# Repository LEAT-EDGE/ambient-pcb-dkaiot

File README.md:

# Ambient DKAIoT Mainboard PCB

Mainboard PCB for the [Ambient project](https://github.com/LEAT-EDGE/ambient).

<div style="display: flex; justify-content: center; gap: 20px;">

</div>

## Main features

- Microcontroller from the STM32L4 or STM32U5 families (LQFP-64 package, no SMPS)
  - STM32L496RG: low-power, Cortex-M4F 80 MHz, 320 KiB SRAM, 1 MiB Flash
  - STM32U595RI: ultra-low-power, Cortex-M33 160 MHz, 2.5 MiB SRAM, 2 MiB Flash
- LoRa modem (Ebyte E22-900M22S)
- GNSS module (Quectel L96-M33)
- Temperature, humidity and pressure (Bosch BME280)
- Micro-SD card reader

The design also provides empty footprints for several other sensors which are not populated in the Ambient variant:
- Light sensor (LITEON LTR-303ALS-01)
- MEMS microphone (Knowles SPH0645LM4H)
- Indoor air quality (Sensirion SGP30)
- Hall effect (Texas Instruments DRV5023AJQLPG)
- Barometer and altimeter (HopeRF HP203B)
- 3-axis accelerometer, 3-axis gyroscope, 3-axis magnetometer (TDK ICM-20948)
- 3-axis accelerometer, 3-axis magnetometer (STMicroelectronics LSM303AH)
- 3-axis accelerometer (Kionix KX023-1025-FR)
- 3-axis accelerometer (Kionix KXTJ3-1057)

## Project structure
- `/` (repository root): KiCad project
- `gerbers/`: Gerbers generated from the KiCad project
- `libraries/`: KiCad libraries of symbols, footprints and 3D models for components not found in the KiCad official repository
- `pdf/`: Schematics generated from the KiCad project
- `png/`: Screenshots of the KiCad 3D render
- `webp/`: Pictures of the actual board

## Firmware

### Firmware sources

Refer to <https://github.com/LEAT-EDGE/ambient-firmware-zephyr> for the new, Zephyr RTOS-based firmware (compatible with both STM32L4 and STM32U5),
and to <https://github.com/LEAT-EDGE/ambient-firmware-arduino> for the old Arduino-based firmware (not compatible with STM32U5).

### Updating the firmware

In order to flash the firmware, put the microcontroller in bootloader DFU mode by holding the BOOT button (right next to the USB port) and pressing the RESET button (next to the BOOT button), then releasing the BOOT button after a couple of seconds. Alternatively, you can hold the BOOT button while plugging the USB cable in, and releasing it after a couple of seconds.

[dfu-util](https://dfu-util.sourceforge.net/) can then be used to update the firmware.
It is called automatically by the `west flash` command when using the Zephyr-based firmware, or by the Arduino IDE's Upload button when using the Arduino-based firmware.

On Windows, for `dfu-util` to work properly, it is recommended to use the WinUSB driver. [Zadig](https://zadig.akeo.ie/) can be used to change the driver of the `STM32 BOOTLOADER` device to WinUSB.

On Linux, for a standard user to have access to the USB device, you may have to install a [udev rules file](https://github.com/LEAT-EDGE/ambient-firmware-arduino/blob/master/stm32dfu.udev.rules) in `/etc/udev/rules.d/`.

An SWD probe (e.g., STLINK V2 or V3) can also be used through the J7 debug header. Programming and debugging can then be performed using [OpenOCD](https://openocd.org/)

## Connectors and headers

### J1: UART

Exposes the `PA2` and `PA3` pins for the `USART2` peripheral of the microcontroller for debugging purposes.

Pinout:

| Pin   | Net           |
|-------|---------------|
| **4** | `V_PERIPH_3V` |
| **3** | `PA2_TX`      |
| **2** | `PA3_RX`      |
| **1** | `GND`         |

### J2J14

Main connector for the [audio capture and energy management daughterboard](https://github.com/LEAT-EDGE/ambient-pcb-audiopower).

Exposes the I2S bus (`SAI1B`), an I2C bus (`I2C2`), the 1.8V (`VDD_1V8`) and 3.0V (`V_PERIPH_3V`) peripheral supplies, 2 GPIOs (`PA10`, `PA15`) and the microcontroller reset signal (`MCU_RESET`, for reed switch reset trigger).

Pinout:

| Pin    | Net           | Pin    | Net            |
|--------|---------------|--------|----------------|
| **11** | `GND`         | **12** | `MCU_RESET`    |
| **9**  | `SAI_FS`      | **10** | `EXT_MIC_IO_2` |
| **7**  | `SAI_SD`      | **8**  | `EXT_MIC_IO_2` |
| **5**  | `SAI_MCLK`    | **6**  | `I2C2_SCL`     |
| **3**  | `SAI_SCK`     | **4**  | `I2C2_SDA`     |
| **1**  | `V_PERIPH_3V` | **2**  | `VDD_1V8`      |

### J3: ADC/DAC

Unused in the Ambient variant.

Exposes 2 GPIOs (`PA5`, `PC2`) that provides access to the microcontroller's ADC and DAC channels.

Pinout:

| Pin   | Net           |
|-------|---------------|
| **2** | `PC2_ADC`     |
| **1** | `PA5_DAC_ADC` |

### J4: BATTERY

Power input to the board and output of the USB charging circuit.

The [audio capture and energy management daughterboard](https://github.com/LEAT-EDGE/ambient-pcb-audiopower) connects to this header with its J3 connector.

| Pin   | Net     |
|-------|---------|
| **2** | `+BATT` |
| **1** | `GND`   |

### J5: SOLAR

Unused in the Ambient variant.

Power input to the charging circuit

Pinout:

| Pin   | Net     |
|-------|---------|
| **2** | `SOLAR` |
| **1** | `GND`   |

### J7: SWD

Exposes the SWD pins of the microcontroller for debugging purposes.

Pinout:

| Pin   | Net         |
|-------|-------------|
| **5** | `3V`        |
| **4** | `SWCLK`     |
| **3** | `MCU_RESET` |
| **2** | `SWDIO`     |
| **1** | `GND`       |

### J11: BATT1

Unused in the Ambient variant.

1st Li-ion cell connector, behind protection circuit.

| Pin   | Net         |
|-------|-------------|
| **2** | `+BATT1_IN` |
| **1** | `-BATT1_IN` |

### J12: BATT2

Unused in the Ambient variant.

2nd Li-ion cell connector, behind protection circuit.

| Pin   | Net         |
|-------|-------------|
| **2** | `+BATT2_IN` |
| **1** | `-BATT2_IN` |

### J20/J21/J22/J23: antenna header

Used to attach the [LoRa antenna mezzanine PCB](https://github.com/LEAT-EDGE/ambient-pcb-antenna).

| Pin     | Net       |
|---------|-----------|
| **J20** | `E22_ANT` |
| **J21** | `GND`     |
| **J22** | `GND`     |
| **J23** | `GND`     |

## Fabrication notes

### PCB

Standard 2-layer 0.8mm stackup:
- 2 layers (front/back),
- 0.8mm thickness,
- 1oz copper,
- FR-4 dielectric,
- HASL finish.

No special requirements, any solder mask and silkscreen color.

Gerbers are provided in the `gerbers/` directory but can be re-generated from the KiCad project.

### Assembly

Recommended automated assembly for top-side only.

Manual assembly for top side:
- J20, J21, J22 and J23 pins (through-hole), to be inserted or cut flush with the back side.

Manual assembly for bottom side:
- C16 and C42 capacitors (SMD),
- J2J14 and J4 connectors (through-hole).

## Testing

Currently, no testing process and firmware is provided. Proper operation of the board can be checked by running the Ambient application firmware.

Short checklist (non exhaustive):
- [ ] USB DFU bootloader detection
- [ ] USB DFU bootloader firmware programming
- [ ] Application firmware boot
- [ ] USB CDC-ACM logs
- [ ] LoRa modem initialization
- [ ] LoRaWAN join
- [ ] LoRaWAN send
- [ ] GNSS time synchronization
- [ ] BME280 temperature read
- [ ] SD card initialization and file write
- [ ] Daughterboard communication:
  - [ ] INA3221 initialization
  - [ ] INA3221 battery/solar current/voltage read
  - [ ] ADC3101 initialization
  - [ ] I2S initialization
  - [ ] I2S audio signal capture

## Acknowledgment

Original circuit design by [@nguyenmanhthao996tn](https://github.com/nguyenmanhthao996tn) in Altium.

The schematics and PCB have been re-designed from scratch in KiCad, while keeping the original circuit ideas, BOM, and component placement to be used as a drop-in replacement.

This project has received funding from [Université Côte d'Azur](https://leat.univ-cotedazur.fr/) and [CERN](https://home.cern/).

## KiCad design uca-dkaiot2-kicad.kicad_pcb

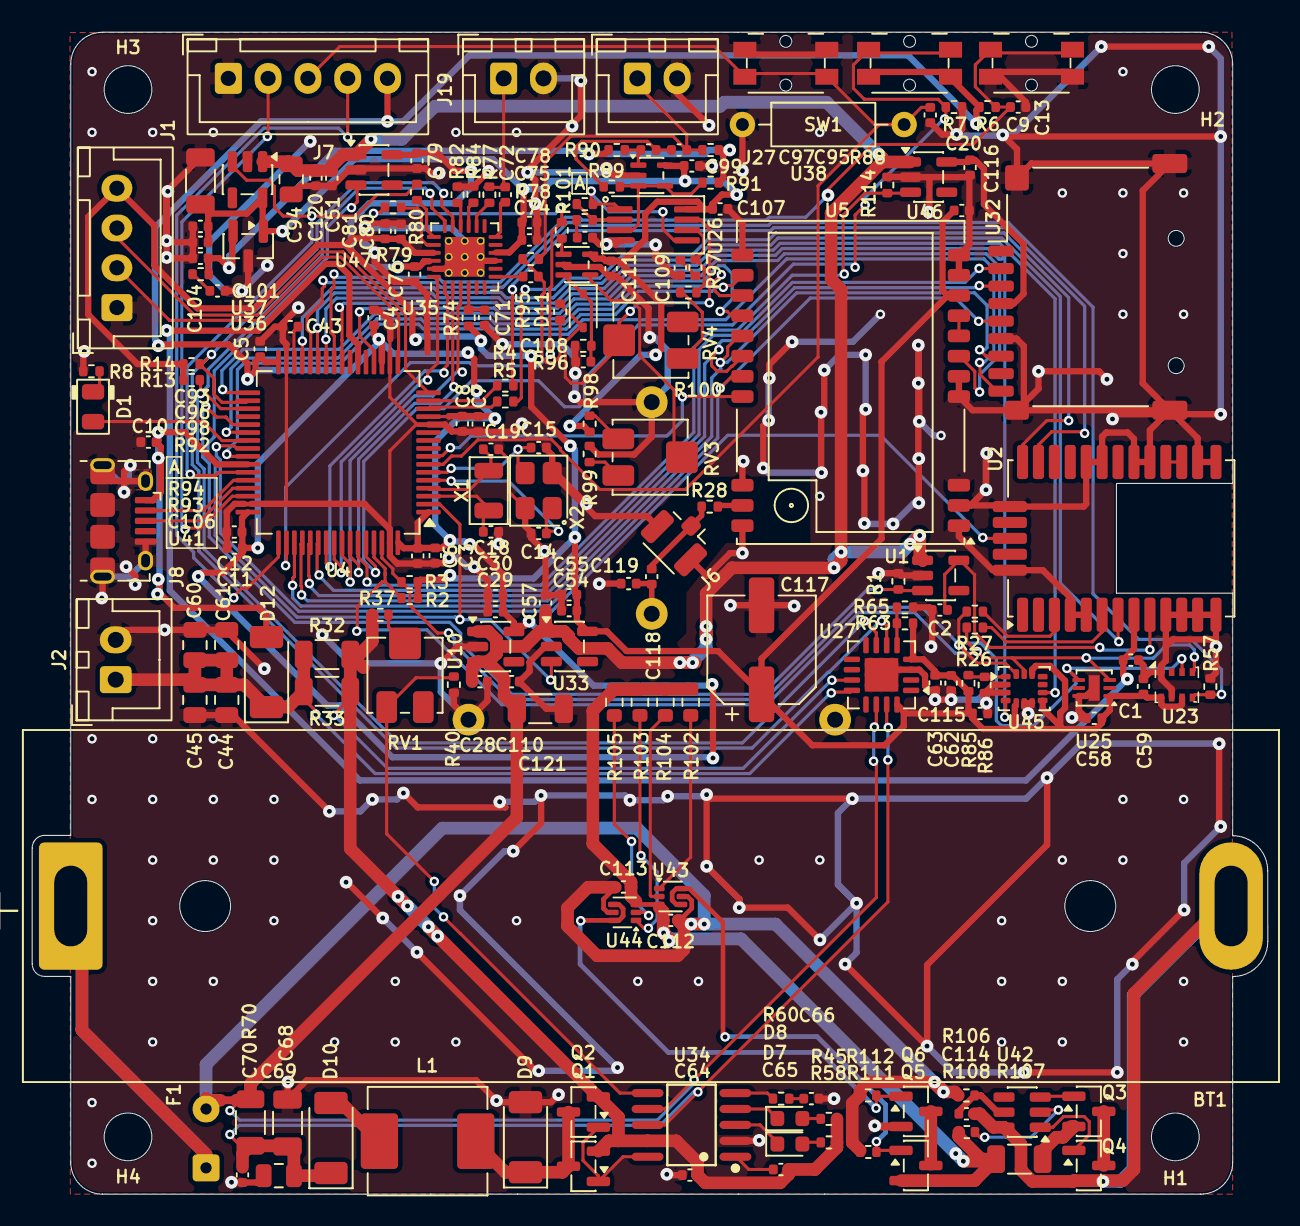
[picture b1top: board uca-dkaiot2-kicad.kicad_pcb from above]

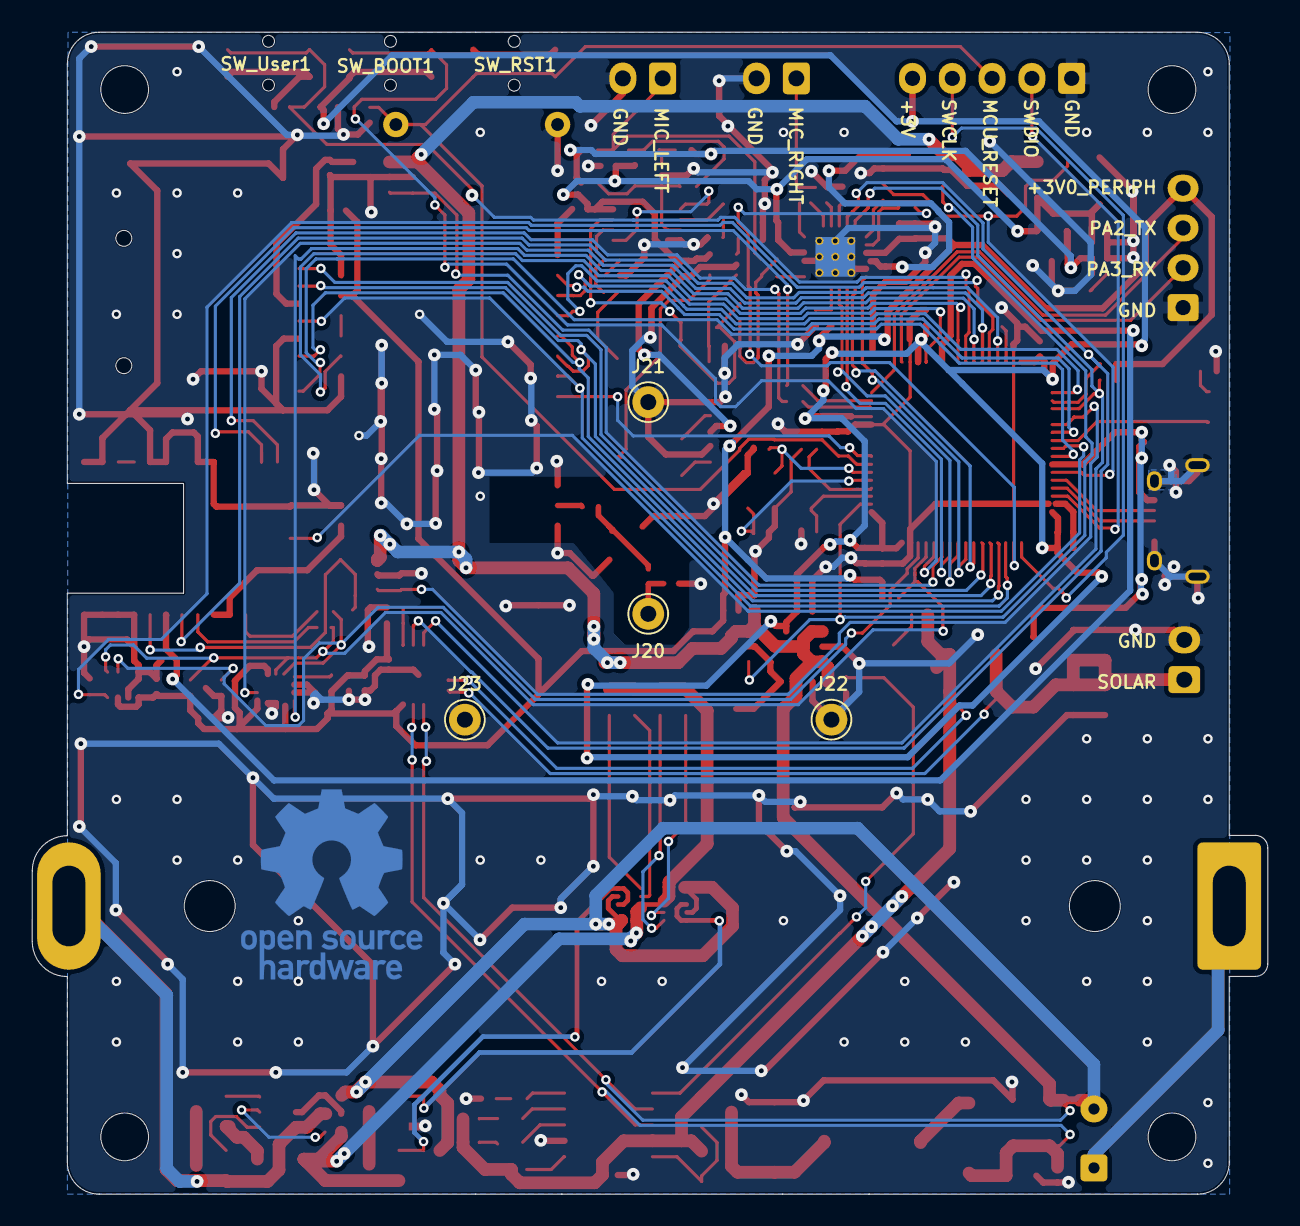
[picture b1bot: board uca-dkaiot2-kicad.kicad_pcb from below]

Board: 4 copper layers, 77.6 x 73.0 mm, 197 parts (5 on the bottom side), 128 nets.

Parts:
BT1: Battery_Cell; BatteryHolder_18650-Ambient
C1, C4, C5, C6, C9, C10, C12, C13, C20, C28, C30, C51, C55, C57, C58, C59, C63, C70, C71, C75, C76, C80, C93, C99, C107, C111, C115: 100nF; C_0402_1005Metric
C2, C3, C7, C11, C29, C43, C54, C62, C79, C96, C101, C110, C116, C120: 4.7µF; C_0402_1005Metric
C8, C95, C97, C98: 10nF; C_0402_1005Metric
C14, C15, C18, C19: 12pF; C_0402_1005Metric
C44, C45, C60, C61: 22µF/25V; C_0805_2012Metric
C64, C65, C112, C113, C114: 100nF/25V; C_0402_1005Metric
C66: 220nF/10V; C_0402_1005Metric
C68, C121: 47µF/10V; C_1206_3216Metric
C69, C94: 4.7µF/10V; C_0805_2012Metric
C72, C74, C78, C81: 1uF; C_0402_1005Metric
C104: 47uF/6.3V; C_1206_3216Metric
C106, C108, C109: 2.2uF; C_0402_1005Metric
C117: 820µF; CP_Elec_6.3x9.9
C118: 2.2pF; C_0402_1005Metric
C119: C_0402_1005Metric
D1: LED_0805_Green; LED_0805_2012Metric
D7: KT-0603R; LED_0603_1608Metric
D8: KT-0603W; LED_0603_1608Metric
D9, D10, D12: PMEG6030ELPX; D_SOD-128
D11: 1N5819WS; D_SOD-323
F1: 3A, 81°C; SolderWire-0.127sqmm_1x02_P3.7mm_D0.48mm_OD1mm
H1, H2, H3, H4: MountingHole; MountingHole_3mm
J1: Conn_01x04; JST_XH_B4B-XH-A_1x04_P2.50mm_Vertical
J2, J19, J27: Conn_01x02; JST_XH_B2B-XH-A_1x02_P2.50mm_Vertical
J6: Conn_Coaxial; U.FL_Hirose_U.FL-R-SMT-1_Vertical_No_Keepout
J7: Conn_01x05; JST_XH_B5B-XH-A_1x05_P2.50mm_Vertical
J8: USB_B_Micro; USB_Micro-B_Amphenol_10118194-0001LF_Horizontal
J20, J21, J22, J23: Conn_01x01; Pin_D1.0mm_L10.0mm
L1: 33µH/2.32A; L_Chilisin_BMRB00060650
NT1, NT2: NetTie_2; NetTie-2_SMD_Pad0.5mm
Q1, Q2: AO3401A; SOT-23
Q3, Q4, Q5, Q6: AO3400A; SOT-23
R1, R2, R3, R6, R13, R14, R74, R93, R97, R100, R114: 4.7k; R_0402_1005Metric
R4, R5: 220; R_0402_1005Metric
R7, R45, R58, R91, R98: 10k; R_0402_1005Metric
R8: 1k; R_0402_1005Metric
R26, R27, R28, R78, R79, R80, R85, R86, R95, R101: 0; R_0402_1005Metric
R32, R33, R70: 0.150; R_1206_3216Metric
R37: 33k; R_0402_1005Metric
R40: 12k; R_0402_1005Metric
R57, R63, R65, R82, R84: 47k; R_0402_1005Metric
R60: 120; R_0402_1005Metric
R77, R88, R92: 2.2k; R_0402_1005Metric
R89: 11k; R_0402_1005Metric
R90: 23k; R_0402_1005Metric
R94, R96, R99: 100k; R_0402_1005Metric
R102: 9.09k; R_0603_1608Metric
R103: 5.90k; R_0603_1608Metric
R104: 38.3k; R_0603_1608Metric
R105: 21.5k; R_0603_1608Metric
R106: 100; R_0402_1005Metric
R107: 0.1; R_1206_3216Metric
R108, R111, R112: 2k; R_0402_1005Metric
RV1, RV3, RV4: 200k; Potentiometer_Bourns_3314J_Vertical
SW1: SW_Reed; R_Axial_DIN0207_L6.3mm_D2.5mm_P10.16mm_Horizontal
SW_BOOT1: SW_Push; Panasonic_EVQPUM_EVQPUD
SW_RST1: SW_Push; Panasonic_EVQPUM_EVQPUD
SW_User1: SW_Push; Panasonic_EVQPUM_EVQPUD
SYM1: Logo_Open_Hardware_Large; OSHW-Logo_11.4x12mm_Copper_SolderMask
U1, U10, U33, U37, U46: RT9080-30GJ5; TSOT-23-5
U2: Quectel_L96
U4: STM32U595RITx; LQFP-64_10x10mm_P0.5mm
U5: E22-900M22S; E22-400M22S
U23: SPA06-003; Bosch_LGA-8_2x2.5mm_P0.65mm_ClockwisePinNumbering
U25: FHTC3; DFN-6-1EP_2x2mm_P0.5mm_EP0.7x1.6mm
U26: OPA2391DGKR; MSOP-8_3x3mm_P0.65mm
U27: INA3221; Texas_RGV0016A_VQFN-16-1EP_4x4mm_P0.65mm_EP2.1x2.1mm
U32: Micro_SD_Card_Det1; microSD_XKB_XKTF-015-x
U34: CN3801; SSOP-10_L4.9-W3.9-P1.00-LS6.0-BL
U35: TLV320ADC3101; VQFN-24-1EP_4x4mm_P0.5mm_EP2.5x2.5mm_ThermalVias_drill0.3
U36: ISL21080CIH315Z-TK; SOT-23
U38: OPA379AIDCK; SOT-353_SC-70-5
U41: TLV7031DCK; SOT-353_SC-70-5
U42: H2112-CB; SOT-23-6
U43, U44: TMP390; SOT-563
U45: LSM6DS3TR-C; LGA-14_3x2.5mm_P0.5mm_LayoutBorder3x4y
U47: RT9080-18GJ5; TSOT-23-5
X1: SMD3225-4; Crystal_SMD_3225-4Pin_3.2x2.5mm
X2: SMD3215-2 32.768kHz; Crystal_SMD_3215-2Pin_3.2x1.5mm

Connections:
+1.5V: C98.1, R88.1, R90.2, R91.2, R92.1, U36.2 (Vout)
+1V8: C76.1, C79.1, U35.22 (DVDD), U47.5 (VOUT)
+3V: C3.1, C4.1, C5.1, C6.1, C7.1, C8.1, C11.1, C12.1, C29.1, C30.1, J7.5, R6.1, SW_BOOT1.2, U4.1 (VBAT), U4.13 (VDDA), U4.19 (VDD), U4.32 (VDD), U4.48 (VDDUSB), U4.64 (VDD), U10.5 (VOUT)
+3V0_PERIPH: C20.1, C54.1, C55.1, C58.1, C59.1, C62.1, C63.1, C80.1, C81.1, C115.1, C117.1, J1.4, R2.2, R3.2, R13.1, R14.1, R63.1, R74.1, R85.1, U5.9 (VCC), U23.6 (VDDIO), U23.8 (VDD), U25.1 (VDD), U27.4 (VS), U27.16 (VPU), U33.5 (VOUT), U35.21 (IOVDD), U45.5 (VDDIO), U45.8 (VDD), U45.12 (CS)
+3V0_SD: C116.1, U32.4 (VDD), U46.5 (VOUT)
+3VSBA: C75.1, C78.1, C93.1, C96.1, C99.1, C104.1, C107.1, C111.1, R98.1, U26.8 (V+), U35.10 (AVDD), U36.1 (Vin), U37.5 (VOUT), U38.5 (V+), U41.5 (V+)
+5V: C10.1, D12.2 (A), J8.1 (VBUS), U4.42 (PA9)
+BATT_PROT: C112.1, C113.1, F1.2, NT1.2, R106.2, R111.2, R112.2, U43.5 (VDD), U44.5 (VDD)
+BATT_UNPROT: BT1.1 (+), F1.1
-BATT_OC_OD_PROT: C112.2, C113.2, Q5.2 (S), R102.2, R103.2, R104.2, R105.2, R107.1, R108.2, U43.3 (GND), U44.3 (GND)
-BATT_PROT: NT2.2, Q6.2 (S)
-BATT_UNPROT: BT1.2 (-), C114.2, Q4.2 (S), U42.6 (VSS)
BUSY_E22: U4.33 (PB12), U5.14 (BUSY)
CSIN: C64.1, C65.1, Q1.2 (S), Q2.2 (S), R32.2, R33.2, R37.1, R45.1, R58.1, U27.11 (IN-1), U34.9 (VCC)
CSIP: C44.1, C45.1, C60.1, C61.1, D12.1 (K), J2.1, R32.1, R33.1, U27.12 (IN+1)
CSON: C28.1, C51.1, C57.1, C94.1, C110.1, C120.1, C121.1, NT1.1, R70.2, U1.1 (VIN), U10.1 (VIN), U10.3 (EN), U27.14 (IN-2), U33.1 (VIN), U34.7 (BAT), U37.1 (VIN), U46.1 (VIN), U47.1 (VIN)
CSOP: C68.1, C69.1, C70.1, D10.1 (K), R70.1, U27.15 (IN+2), U34.8 (CSP)
DIO1_E22: U4.38 (PC7), U5.13 (DIO1)
E22_ANT: R28.1, U5.21 (ANT)
EXT_MIC_IO_1: R80.2, U4.43 (PA10), U37.3 (EN)
EXT_MIC_IO_2: R79.2, R101.1, U4.50 (PA15)
GND: C1.2, C2.2, C3.2, C4.2, C5.2, C6.2, C7.2, C8.2, C9.2, C10.2, C11.2, C12.2, C13.2, C14.2, C15.2, C18.2, C19.2, C20.2, C28.2, C29.2, C30.2, C43.2, C44.2, C45.2, C51.2, C54.2, C55.2, C57.2, C58.2, C59.2, C60.2, C61.2, C62.2, C63.2, C64.2, C66.2, C68.2, C69.2, C70.2, C71.2, C75.2, C76.2, C78.2, C79.2, C80.2, C81.2, C93.2, C94.2, C96.2, C98.2, C99.2, C101.2, C104.2, C106.1, C107.2, C108.1, C109.1, C110.2, C111.2, C115.2, C116.2, C117.2, C119.2, C120.2, C121.2, D9.2 (A), J1.1, J2.2, J6.2 (Ext), J7.1, J8.5 (GND), J8.SH (Shield), J19.2, J21.1 (Pin_1_1), J22.1 (Pin_1_1), J23.1 (Pin_1_1), J27.2, NT2.1, R1.2, R7.2, R8.2, R40.2, R57.2, R65.2, R82.2, R84.2, R86.2, R96.2, R99.2, R114.2, SW1.1, SW_RST1.1, SW_User1.2, SYM1.1 (1_1), U1.2 (GND), U2.4 (GND), U2.5 (GND), U2.10 (GND), U2.11 (GND), U2.12 (GND), U2.13 (GND), U2.14 (GND), U2.15 (GND), U2.18 (GND), U2.19 (GND), U2.21 (GND), U2.22 (GND), U2.27 (GND), U2.31 (GND), U4.12 (VSSA), U4.18 (VSS), U4.31 (VSS), U4.47 (VSS), U4.63 (VSS), U5.1 (GND), U5.2 (GND), U5.3 (GND), U5.4 (GND), U5.5 (GND), U5.10 (GND), U5.11 (GND), U5.12 (GND), U5.20 (GND), U5.22 (GND), U10.2 (GND), U23.1 (GND), U23.7 (GND), U25.6 (GND), U25.7 (EPAD), U26.4 (V-), U27.3 (GND), U27.17 (EP), U32.6 (VSS), U32.SH (SHIELD), U33.2 (GND), U34.2 (GND), U35.9 (AVSS), U35.23 (DVSS), U35.25 (PAD), U36.3 (GND), U37.2 (GND), U38.2 (V-), U41.2 (V-), U45.2 (SDX), U45.3 (SCX), U45.6 (GND), U45.7 (GND), U46.2 (GND), U47.2 (GND), X1.2, X1.4
GPS_INT: U2.7 (EXTINT0), U4.29 (PB10)
GPS_On_Off: R1.1, U1.3 (EN), U4.37 (PC6)
GPS_RXD: R5.1, U4.14 (PA0)
GPS_TXD: R4.1, U4.15 (PA1)
I2C1_SCL: R2.1, R26.1, U4.61 (PB8), U23.4 (SCK), U25.3 (SCL), U45.13 (SCL)
I2C1_SDA: R3.1, R27.1, U4.62 (PB9), U23.3 (SDI), U25.4 (SDA), U45.14 (SDA)
I2C2_SCL: R14.2, U4.34 (PB13), U27.6 (SCL), U35.17 (SCL)
I2C2_SDA: R13.2, U4.35 (PB14), U27.7 (SDA), U35.18 (SDA)
IN2L(P): C74.2, R78.2, R95.2
INT_ACC_1: U4.26 (PB0), U45.4 (INT1)
INT_ACC_2: U4.27 (PB1), U45.9 (INT2)
INT_ACC_3: R57.1, U4.28 (PB2), U23.5 (SDO)
LED: D1.2 (A), U4.39 (PC8)
MCU_RESET: C13.1, J7.3, SW1.2, SW_RST1.2, U4.7 (NRST)
MIC_LEFT: C95.1, J27.1, R78.1, R88.2
MISO_E22: U4.52 (PC11), U5.16 (MISO), U32.7 (DAT0)
MOSI_E22: U4.53 (PC12), U5.17 (MOSI), U32.3 (CMD)
NRST_E22: U4.20 (PA4), U5.15 (NRST)
NSS_E22: U4.8 (PC0), U5.19 (NSS)
unnamed: C66.1, R60.2
unnamed: C95.2, C97.1, R89.2
unnamed: C101.1, R92.2
unnamed: C106.2, R93.2
unnamed: C109.2, R97.2
unnamed: D1.1 (K), R8.1
unnamed: D7.2 (A), R58.2
unnamed: D7.1 (K), U34.3 (~CHRG)
unnamed: D8.2 (A), R45.2
unnamed: D8.1 (K), U34.4 (~DONE)
unnamed: D9.1 (K), L1.1, Q1.3 (D), Q2.3 (D)
unnamed: D10.2 (A), L1.2
unnamed: D11.2 (A), R95.1, RV4.2, U26.7
unnamed: C108.2, D11.1 (K), R96.1, U41.3 (+)
unnamed: C118.1, J6.1 (In), R28.2
unnamed: C72.1, J19.1, R77.2
unnamed: C118.2, C119.1, J20.1 (Pin_1_1)
unnamed: Q1.1 (G), Q2.1 (G), U34.10 (DRV)
unnamed: Q3.3 (D), Q4.3 (D)
unnamed: Q3.1 (G), U42.3 (OC)
unnamed: Q3.2 (S), R107.2
unnamed: Q4.1 (G), U42.1 (OD)
unnamed: Q5.3 (D), Q6.3 (D)
unnamed: Q5.1 (G), R111.1, U43.4 (~OUTB), U43.6 (~OUTA)
unnamed: Q6.1 (G), R112.1, U44.4 (~OUTB), U44.6 (~OUTA)
unnamed: R37.2, RV1.2
unnamed: R98.2, RV3.1
unnamed: R99.1, RV3.3
unnamed: R100.2, RV4.1
unnamed: R101.2, U41.1
unnamed: C2.1, U1.5 (VOUT), U2.9 (VCC)
unnamed: U2.16 (RF_OUT), U2.17 (RF_IN)
unnamed: R5.2, U2.26 (RXD1)
unnamed: R26.2, U2.6 (SCL)
unnamed: R27.2, U2.3 (SDA)
unnamed: R4.2, U2.25 (TXD1)
unnamed: C18.1, U4.3 (PC14), X2.1
unnamed: C19.1, U4.4 (PC15), X2.2
unnamed: C14.1, U4.5 (PH0), X1.1
unnamed: C15.1, U4.6 (PH1), X1.3
unnamed: R7.1, SW_BOOT1.1, U4.60 (PH3)
unnamed: C43.1, U4.30 (VCAP)
unnamed: U5.7 (TXEN), U5.8 (DIO2)
unnamed: R89.1, R91.1, U26.3 (+), U38.3 (-), U38.4
unnamed: R93.1, R94.1, U26.2 (-)
unnamed: R94.2, U26.1, U26.5 (+)
unnamed: R97.1, R100.1, U26.6 (-)
unnamed: R63.2, R65.1, U27.5 (A0)
unnamed: R60.1, U34.5 (COM)
unnamed: R40.1, RV1.1, U34.6 (MPPT)
unnamed: C65.2, U34.1 (VG)
unnamed: R79.1, U35.20 (DMCLK/G2)
unnamed: R80.1, U35.19 (DMDIN/G1)
unnamed: R84.1, U35.15 (I2C_ADR0)
unnamed: R82.1, U35.16 (I2C_ADR1)
unnamed: C74.1, U35.7 (IN2L(P))
unnamed: C72.2, U35.12 (IN2R(P))
unnamed: R77.1, U35.14 (MICBIAS2)
unnamed: C71.1, R74.2, U35.4 (~RESET)
unnamed: C97.2, R90.1, U38.1 (+)
unnamed: RV3.2, U41.4 (-)
unnamed: R108.1, U42.2 (CS)
unnamed: C114.1, R106.1, U42.5 (VDD)
unnamed: R102.1, U43.1 (SETA)
unnamed: R104.1, U43.2 (SETB)
unnamed: R103.1, U44.1 (SETA)
unnamed: R105.1, U44.2 (SETB)
unnamed: R85.2, R86.1, U45.1 (SDO/SA0)
PA2_TX: J1.3, U4.16 (PA2)
PA3_RX: J1.2, U4.17 (PA3)
RXEN_E22: U4.24 (PC4), U5.6 (RXEN)
SAI_FS: U4.58 (PB6), U35.2 (WCLK)
SAI_MCLK: U4.56 (PB4), U35.24 (MCLK)
SAI_SCK: U4.55 (PB3), U35.1 (BCLK)
SAI_SD: U4.57 (PB5), U35.3 (DOUT)
SCK_E22: U4.51 (PC10), U5.18 (SCK), U32.5 (CLK)
SD_CD: U4.41 (PA8), U32.9 (DET)
SD_ON_OFF: R114.1, U4.59 (PB7), U46.3 (EN)
SD_SS: U4.54 (PD2), U32.2 (DAT3/CD)
SWCLK: J7.4, U4.49 (PA14)
SWDIO: J7.2, U4.46 (PA13)
TIMEPULSE: U2.29 (TIMEPULSE), U4.40 (PC9)
USB+: J8.3 (D+), U4.45 (PA12)
USB-: J8.2 (D-), U4.44 (PA11)
UserButton: C9.1, R6.2, SW_User1.1, U4.25 (PC5)
V_BCKP_On_Off: C1.1, U2.8 (V_BCKP), U4.22 (PA6)
V_PERIPH_CTRL: U4.2 (PC13), U33.3 (EN), U47.3 (EN)

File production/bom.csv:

Designator,Footprint,Quantity,Value,LCSC Part #
"C1, C10, C107, C111, C115, C12, C13, C20, C28, C30, C4, C5, C51, C55, C57, C58, C59, C6, C63, C70, C71, C75, C76, C80, C9, C93, C99",0402,27,100nF,C1525
"C101, C11, C110, C116, C120, C2, C29, C3, C43, C54, C62, C7, C79, C96",0402,14,4.7µF,C23733
C104,1206,1,47uF/6.3V,C96123
"C106, C108, C109",0402,3,2.2uF,C12530
"C112, C113, C114, C64, C65",0402,5,100nF/25V,C307331
C117,CP_Elec_6.3x9.9,1,820µF,C55145369
C118,0402,1,2.2pF,C1559
"C121, C68",1206,2,47µF/10V,C96123
"C14, C15, C18, C19",0402,4,12pF,C1547
"C44, C45, C60, C61",0805,4,22µF/25V,C45783
C66,0402,1,220nF/10V,C16772
"C69, C94",0805,2,4.7µF/10V,C1779
"C72, C74, C78, C81",0402,4,1uF,C52923
"C8, C95, C97, C98",0402,4,10nF,C15195
D1,0805,1,LED_0805_Green,C2297
"D10, D12, D9",D_SOD-128,3,PMEG6030ELPX,C2908821
D11,D_SOD-323,1,1N5819WS,C191023
D7,0603,1,KT-0603R,C2286
D8,0603,1,KT-0603W,C2290
F1,SolderWire-0.127sqmm_1x02_P3.7mm_D0.48mm_OD1mm,1,"3A, 81°C",C3032558
"J2, J27",JST_XH_B2B-XH-A_1x02_P2.50mm_Vertical,2,Conn_01x02,C20079
"J20, J21, J22, J23",Pin_D1.0mm_L10.0mm,4,Conn_01x01,C25503131
J6,U.FL_Hirose_U.FL-R-SMT-1_Vertical_No_Keepout,1,Conn_Coaxial,C88373
J8,USB_Micro-B_Amphenol_10118194-0001LF_Horizontal,1,USB_B_Micro,C132563
L1,L_Chilisin_BMRB00060650,1,33µH/2.32A,C47327223
"Q1, Q2",SOT-23,2,AO3401A,C15127
"Q3, Q4, Q5, Q6",SOT-23,4,AO3400A,C20917
"R1, R100, R114, R13, R14, R2, R3, R6, R74, R93, R97",0402,11,4.7k,C25900
"R101, R26, R27, R28, R78, R86",0402,6,0,C17168
R102,0603,1,9.09k,C23260
R103,0603,1,5.90k,C4260
R104,0603,1,38.3k,C23153
R105,0603,1,21.5k,C31850
R106,0402,1,100,C25076
R107,1206,1,0.1,C25334
"R108, R111, R112",0402,3,2k,C4109
"R32, R33, R70",1206,3,0.150,C2683383
R37,0402,1,33k,C25779
"R4, R5",0402,2,220,C25091
R40,0402,1,12k,C25752
"R45, R58, R7, R91, R98",0402,5,10k,C25744
R60,0402,1,120,C25079
"R65, R82, R84",0402,3,47k,C25792
"R77, R88, R92",0402,3,2.2k,C25879
R8,0402,1,1k,C11702
R89,0402,1,11k,C25744
R90,0402,1,23k,C25768
"R94, R96, R99",0402,3,100k,C25741
"RV1, RV3, RV4",Potentiometer_Bourns_3314J_Vertical,3,200k,C124643
"SW_BOOT1, SW_RST1, SW_USER1",Panasonic_EVQPUM_EVQPUD,3,SW_Push,C223812
"U1, U10, U33, U37, U46",TSOT-23-5,5,RT9080-30GJ5,C965900
U2,Quectel_L96,1,Quectel_L96,C5197298
U23,Bosch_LGA-8_2x2.5mm_P0.65mm_ClockwisePinNumbering,1,SPA06-003,C30589048
U25,DFN-6-1EP_2x2mm_P0.5mm_EP0.7x1.6mm,1,FHTC3,C51901044
U26,MSOP-8_3x3mm_P0.65mm,1,OPA2391DGKR,C44383322
U27,Texas_RGV0016A_VQFN-16-1EP_4x4mm_P0.65mm_EP2.1x2.1mm,1,INA3221,C181255
U32,microSD_XKB_XKTF-015-x,1,Micro_SD_Card_Det1,C22383473
U34,SSOP-10_L4.9-W3.9-P1.00-LS6.0-BL,1,CN3801,C840499
U35,VQFN-24-1EP_4x4mm_P0.5mm_EP2.5x2.5mm_ThermalVias_drill0.3,1,TLV320ADC3101,C162409
U36,SOT-23,1,ISL21080CIH315Z-TK,C128623
U38,SOT-353_SC-70-5,1,OPA379AIDCK,C576302
U4,LQFP-64_10x10mm_P0.5mm,1,STM32U595RITx,C28563722
U41,SOT-353_SC-70-5,1,TLV7031DCK,C2863637
U42,SOT-23-6,1,H2112-CB,C168764
"U43, U44",SOT-563,2,TMP390,C5219772
U45,LGA-14_3x2.5mm_P0.5mm_LayoutBorder3x4y,1,LSM6DS3TR-C,C967633
U47,TSOT-23-5,1,RT9080-18GJ5,C426476
U5,E22-400M22S,1,E22-900M22S,C411293
X1,Crystal_SMD_3225-4Pin_3.2x2.5mm,1,SMD3225-4,C13738
X2,Crystal_SMD_3215-2Pin_3.2x1.5mm,1,SMD3215-2 32.768kHz,C32346

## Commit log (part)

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2026-05-26 Add symbol libraries for Ebyte E22, Kionix KX023, Onsemi NCV8170, Quectel L96, ST LSM303AH
2026-05-26 WIP: KiCad project
2026-05-27 Add symbol libraries for HOPERF HP203B, Nisshibo R5478N, Sensirion SGP30
2026-05-27 Add footprint library for Sensirion DFN-6 2.44x2.44mm P0.8mm
2026-05-27 Continue filling schematics
2026-05-27 libraries/Onsemi_NCV8170.kicad_sym: fix part number in symbol for B variant
2026-05-28 libraries: update footprint filter for Kionix_KX023, Onsemi_NCV8170 and Sensirion_SGP30
2026-05-28 Add E22-400M22S footprint
2026-05-28 Add footprints microSD_XKB_XKTF-015-x BAT-TH_BH-18650-A1BJ034
2026-05-28 Finalize schematics as AIoT2-rev003-May1326
2026-05-28 Schematics Ambient variant with unneeded sensors DNP
2026-05-29 footprint: microSD_XKB_XKTF-015-x pin 10 → SH
2026-05-29 Add footprint for HP203B
2026-05-29 symbol: SGP30: fix center pad pin number
2026-05-29 PCB component placement according to AIoT2
2026-06-01 pcb: 2-layer stackup
2026-06-01 pcb: remove original AIoT2 design
2026-06-01 pcb: start 2-layer routing
2026-06-02 pcb: continue routing
2026-06-04 Add 3dmodels for E22-400M22S L96_M33 MICRO-USB-SMD_MICRO-XNJ-ZB TF-SMD_TF-01A
2026-06-04 symbol: Kionix_KX023 add hidden NC pads
2026-06-04 schematics: add some DNP for Ambient variant
2026-06-04 pcb: silkscreen placement and some cleanup
2026-06-04 pcb: disable Pad to Silkscreen clearance rule
2026-06-04 pcb: 1 minimum spoke for thermal relief, silkscreen clearance reduced to 0.05, add some DRC exclusions
2026-06-04 pcb: pins for antenna, silkscreen…
2026-06-04 pcb: via stitching
2026-06-04 pcb: some fixes
2026-06-05 Add OSHW logo
2026-06-05 Add pdf/ gerbers/
2026-06-05 pdf: Ambient variant
2026-06-05 OSHW logo tied to ground net
2026-06-05 Add png/
2026-06-05 pdf: update
2026-06-14 v0.2: fix Ebyte E22-900M22S pinout
2026-06-14 Move symbols to libraries/symbols/
2026-06-14 pcb: fix revision number text
2026-06-14 Add webp/
2026-06-14 Add README.md
2026-06-14 Add LICENSE.txt
2026-06-14 README.md: fix picture alt text
2026-06-14 README.md: typo
